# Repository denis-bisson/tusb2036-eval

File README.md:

Evaluation board for the TI TUSB2036 USB hub controller.

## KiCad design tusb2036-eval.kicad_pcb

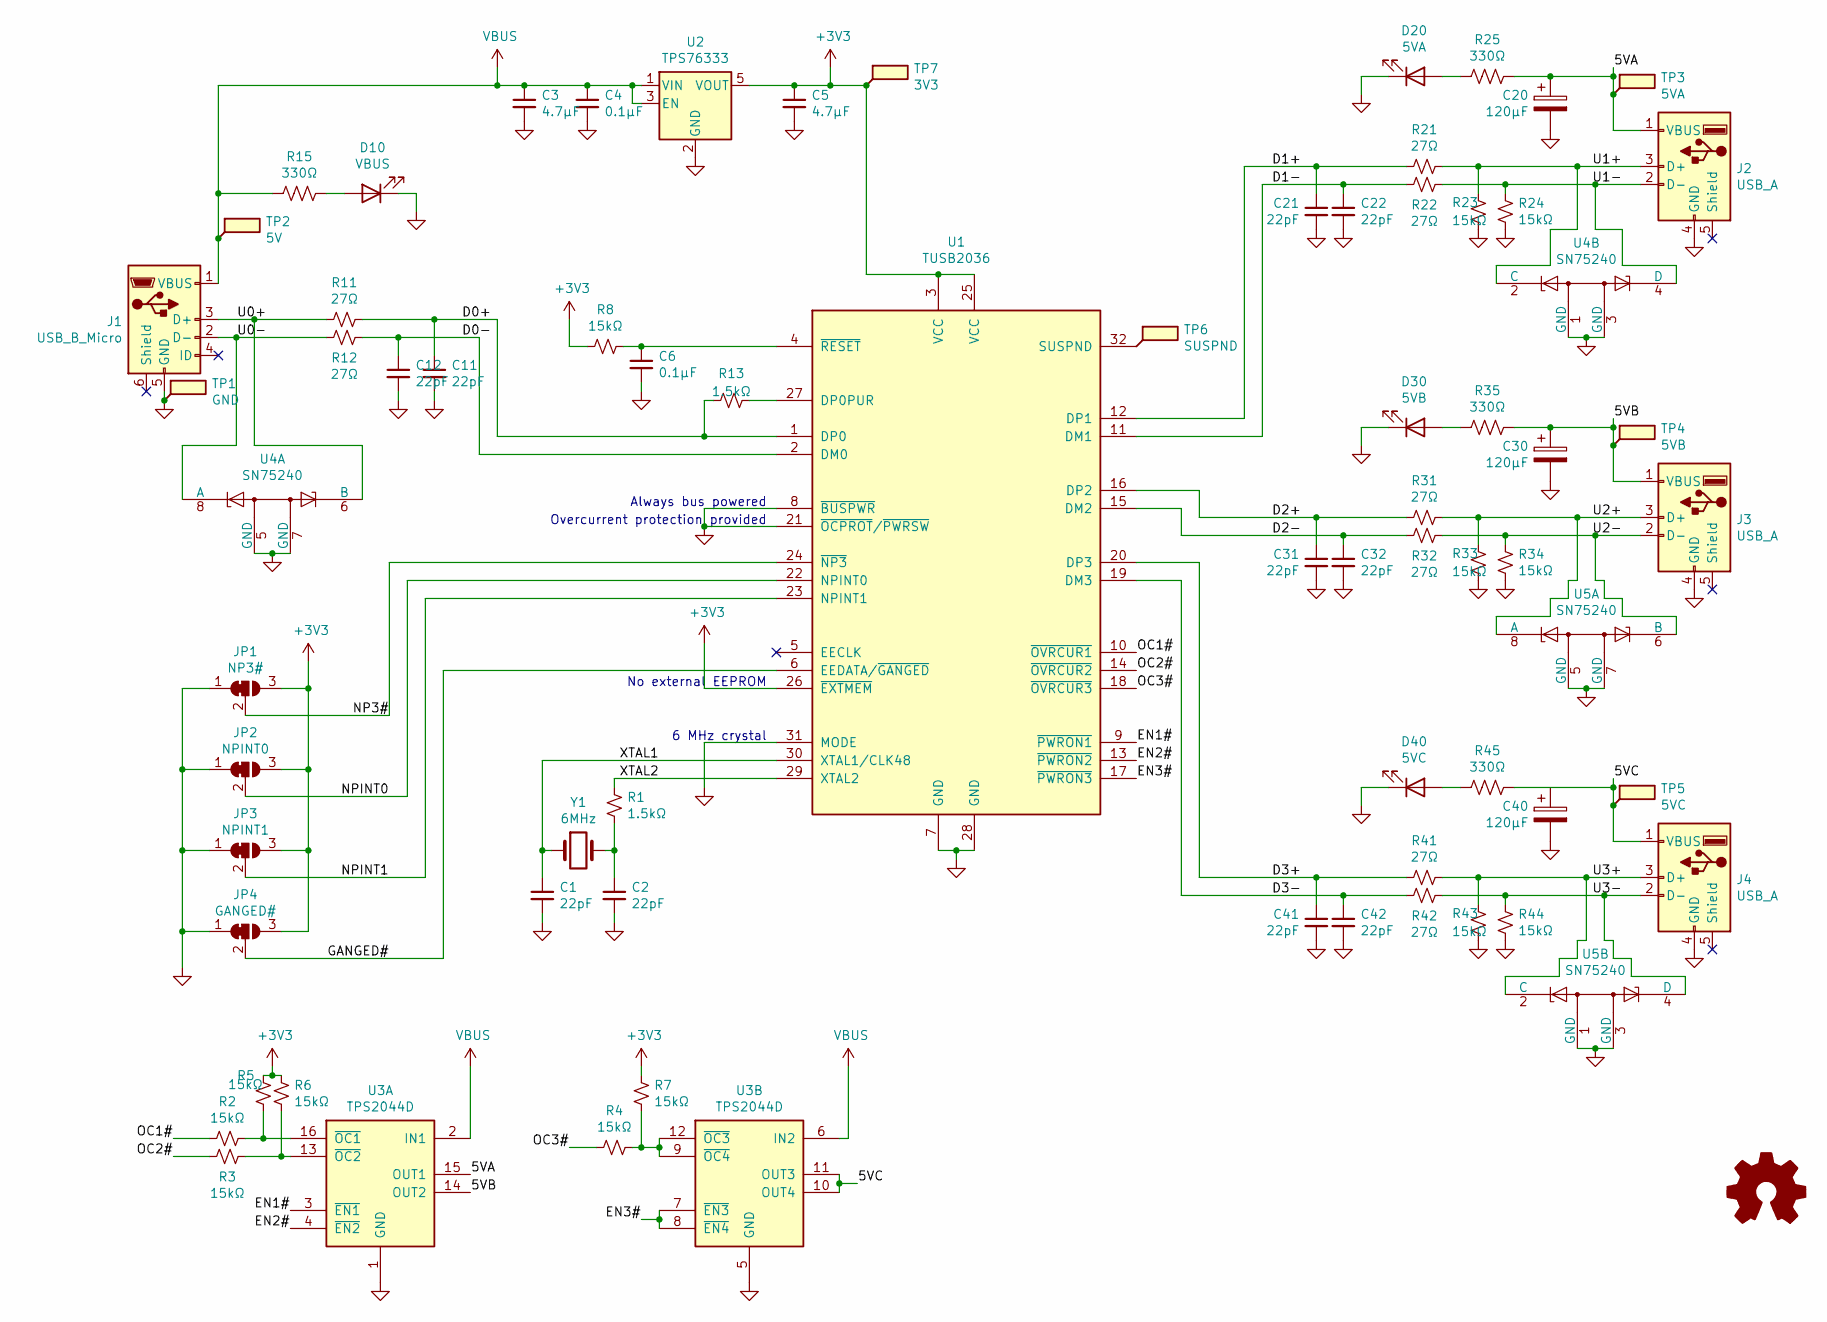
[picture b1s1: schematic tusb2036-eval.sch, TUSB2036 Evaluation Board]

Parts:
C1, C2, C11, C12, C21, C22, C31, C32, C41, C42: 22pF; C_1206_3216Metric
C3, C5: 4.7μF; C_1206_3216Metric
C4, C6: 0.1μF; C_1206_3216Metric
C20, C30, C40: 120μF; CAPPM7343X310N
D10: VBUS; LED_1206_3216Metric
D20: 5VA; LED_1206_3216Metric
D30: 5VB; LED_1206_3216Metric
D40: 5VC; LED_1206_3216Metric
J1: USB_B_Micro; UJ2-MIBH-4-SMT
J2, J3, J4: USB_A; 62900416021
JP1: NP3#; PinHeader_1x03_P2.54mm_Vertical
JP2: NPINT0; PinHeader_1x03_P2.54mm_Vertical
JP3: NPINT1; PinHeader_1x03_P2.54mm_Vertical
JP4: GANGED#; PinHeader_1x03_P2.54mm_Vertical
LOGO1: Logo_Open_Hardware_Small; OSHW-Logo2_9.8x8mm_SilkScreen
R1, R13: 1.5kΩ; R_1206_3216Metric
R2, R3, R4, R5, R6, R7, R8, R23, R24, R33, R34, R43, R44: 15kΩ; R_1206_3216Metric
R11, R12, R21, R22, R31, R32, R41, R42: 27Ω; R_1206_3216Metric
R15, R25, R35, R45: 330Ω; R_1206_3216Metric
TP1: GND; TestPoint_Pad_D2.0mm
TP2: 5V; TestPoint_Pad_D2.0mm
TP3: 5VA; TestPoint_Pad_D2.0mm
TP4: 5VB; TestPoint_Pad_D2.0mm
TP5: 5VC; TestPoint_Pad_D2.0mm
TP6: SUSPND; TestPoint_Pad_D2.0mm
TP7: 3V3; TestPoint_Pad_D2.0mm
U1: TUSB2036; LQFP-32_7x7mm_P0.8mm
U2: TPS76333; SOT-23-5
U3: TPS2044D; SOIC-16_3.9x9.9mm_P1.27mm
U4, U5: SN75240; TSSOP-8_4.4x3mm_P0.65mm
Y1: 6MHz; Crystal_SMD_HC49-SD

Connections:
+3V3: C5.1, JP1.3 (B), JP2.3 (B), JP3.3 (B), JP4.3 (B), R5.2, R6.2, R7.2, R8.2, TP7.1, U1.3 (VCC), U1.25 (VCC), U1.26 (~EXTMEM), U2.5 (VOUT)
/5VA: C20.1, J2.1 (VBUS), R25.1, TP3.1, U3.15 (OUT1)
/5VB: C30.1, J3.1 (VBUS), R35.1, TP4.1, U3.14 (OUT2)
/5VC: C40.1, J4.1 (VBUS), R45.1, TP5.1, U3.10 (OUT4), U3.11 (OUT3)
/D0+: C11.1, R11.2, R13.2, U1.1 (DP0)
/D0-: C12.1, R12.2, U1.2 (DM0)
/D1+: C21.1, R21.1, U1.12 (DP1)
/D1-: C22.1, R22.1, U1.11 (DM1)
/D2+: C31.1, R31.1, U1.16 (DP2)
/D2-: C32.1, R32.1, U1.15 (DM2)
/D3+: C41.1, R41.1, U1.20 (DP3)
/D3-: C42.1, R42.1, U1.19 (DM3)
/EN1#: U1.9 (~PWRON1), U3.3 (~EN1)
/EN2#: U1.13 (~PWRON2), U3.4 (~EN2)
/EN3#: U1.17 (~PWRON3), U3.7 (~EN3), U3.8 (~EN4)
/GANGED#: JP4.2 (C), U1.6 (EEDATA/~GANGED)
/NP3#: JP1.2 (C), U1.24 (~NP3)
/NPINT0: JP2.2 (C), U1.22 (NPINT0)
/NPINT1: JP3.2 (C), U1.23 (NPINT1)
/OC1#: R2.2, U1.10 (~OVRCUR1)
/OC2#: R3.2, U1.14 (~OVRCUR2)
/OC3#: R4.2, U1.18 (~OVRCUR3)
/U0+: J1.3 (D+), R11.1, U4.6 (B)
/U0-: J1.2 (D-), R12.1, U4.8 (A)
/U1+: J2.3 (D+), R21.2, R23.1, U4.2 (C)
/U1-: J2.2 (D-), R22.2, R24.1, U4.4 (D)
/U2+: J3.3 (D+), R31.2, R33.1, U5.8 (A)
/U2-: J3.2 (D-), R32.2, R34.1, U5.6 (B)
/U3+: J4.3 (D+), R41.2, R43.1, U5.2 (C)
/U3-: J4.2 (D-), R42.2, R44.1, U5.4 (D)
/XTAL1: C1.1, U1.30 (XTAL1/CLK48), Y1.1
/XTAL2: R1.1, U1.29 (XTAL2)
GND: C1.2, C2.2, C3.2, C4.2, C5.2, C6.2, C11.2, C12.2, C20.2, C21.2, C22.2, C30.2, C31.2, C32.2, C40.2, C41.2, C42.2, D10.1 (K), D20.1 (K), D30.1 (K), D40.1 (K), J1.5 (GND), J2.4 (GND), J3.4 (GND), J4.4 (GND), JP1.1 (A), JP2.1 (A), JP3.1 (A), JP4.1 (A), R23.2, R24.2, R33.2, R34.2, R43.2, R44.2, TP1.1, U1.7 (GND), U1.8 (~BUSPWR), U1.21 (~OCPROT~/~PWRSW~), U1.28 (GND), U1.31 (MODE), U2.2 (GND), U3.1 (GND), U3.5 (GND), U4.1 (GND), U4.3 (GND), U4.5 (GND), U4.7 (GND), U5.1 (GND), U5.3 (GND), U5.5 (GND), U5.7 (GND)
unnamed: C2.1, R1.2, Y1.2
unnamed: C6.1, R8.1, U1.4 (~RESET)
unnamed: D10.2 (A), R15.1
unnamed: D20.2 (A), R25.2
unnamed: D30.2 (A), R35.2
unnamed: D40.2 (A), R45.2
unnamed: R2.1, R5.1, U3.16 (~OC1)
unnamed: R3.1, R6.1, U3.13 (~OC2)
unnamed: R4.1, R7.1, U3.9 (~OC4), U3.12 (~OC3)
unnamed: R13.1, U1.27 (DP0PUR)
unnamed: TP6.1, U1.32 (SUSPND)
VBUS: C3.1, C4.1, J1.1 (VBUS), R15.2, TP2.1, U2.1 (VIN), U2.3 (EN), U3.2 (IN1), U3.6 (IN2)

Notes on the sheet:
Always bus powered
Overcurrent protection provided
No external EEPROM
6 MHz crystal

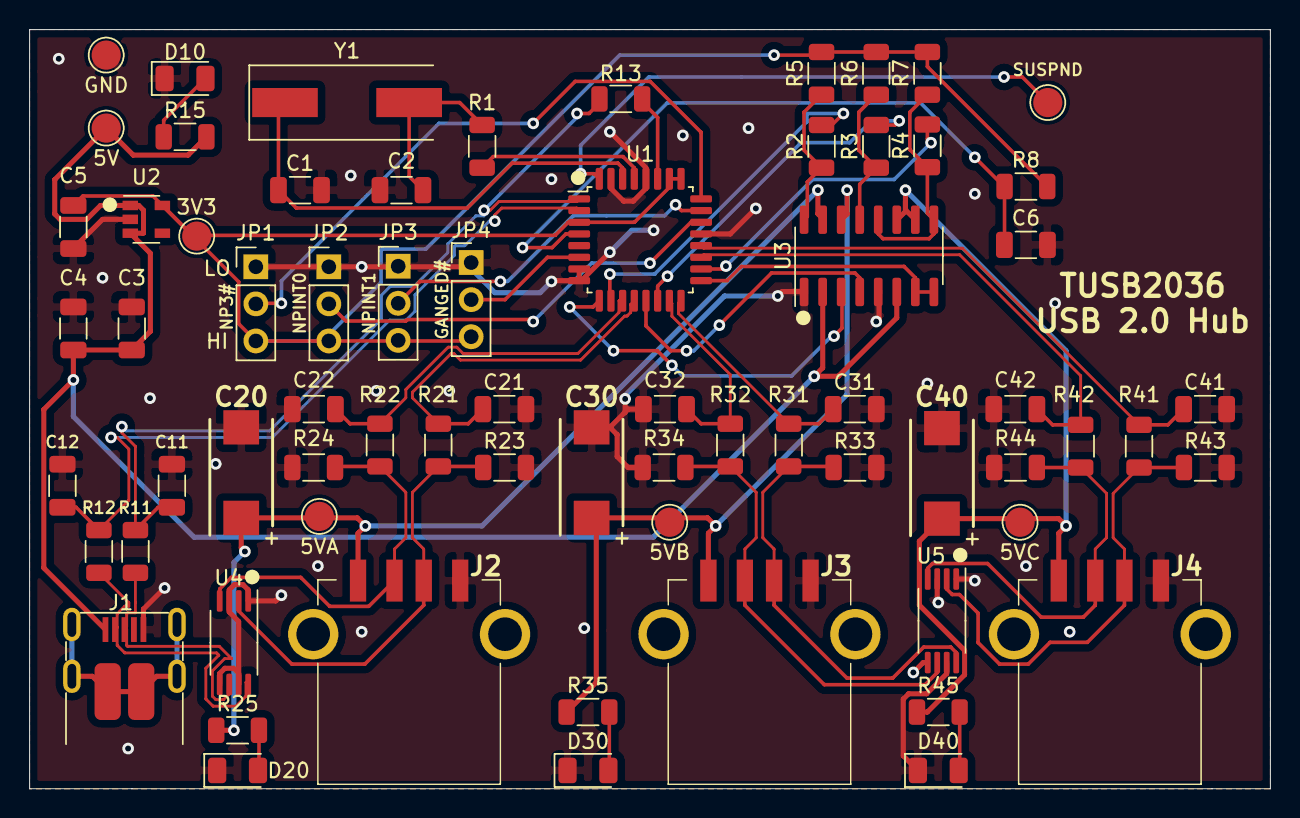
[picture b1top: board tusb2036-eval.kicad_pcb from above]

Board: 2 copper layers, 85.0 x 52.0 mm, 70 parts (1 on the bottom side), 45 nets.

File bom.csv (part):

Refs,value,Vendor,Vendor Part #,Price,datasheet,footprint
C1,22pF,Mouser,710-885012009007,0.61,https://www.mouser.com/datasheet/2/445/885012009007-1727300.pdf,Capacitor_SMD:C_1206_3216Metric
C10,22pF,Mouser,710-885012009007,0.61,https://www.mouser.com/datasheet/2/445/885012009007-1727300.pdf,Capacitor_SMD:C_1206_3216Metric
C11,22pF,Mouser,710-885012009007,0.61,https://www.mouser.com/datasheet/2/445/885012009007-1727300.pdf,Capacitor_SMD:C_1206_3216Metric
C2,22pF,Mouser,710-885012009007,0.61,https://www.mouser.com/datasheet/2/445/885012009007-1727300.pdf,Capacitor_SMD:C_1206_3216Metric
C20,120μF,Mouser,74-293D127X96R3D2TE3,0.87,https://www.mouser.com/datasheet/2/427/293d-1763499.pdf,Vishay:CAPPM7343X310N
C21,22pF,Mouser,710-885012009007,0.61,https://www.mouser.com/datasheet/2/445/885012009007-1727300.pdf,Capacitor_SMD:C_1206_3216Metric
C22,22pF,Mouser,710-885012009007,0.61,https://www.mouser.com/datasheet/2/445/885012009007-1727300.pdf,Capacitor_SMD:C_1206_3216Metric
C3,4.7μF,Mouser,80-C1210C475J3N,0.93,https://www.mouser.com/datasheet/2/212/KEM_C1008_X8L_150C_SM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,Capacitor_SMD:C_1206_3216Metric
C30,120μF,Mouser,74-293D127X96R3D2TE3,0.87,https://www.mouser.com/datasheet/2/427/293d-1763499.pdf,Vishay:CAPPM7343X310N
C31,22pF,Mouser,710-885012009007,0.61,https://www.mouser.com/datasheet/2/445/885012009007-1727300.pdf,Capacitor_SMD:C_1206_3216Metric
C32,22pF,Mouser,710-885012009007,0.61,https://www.mouser.com/datasheet/2/445/885012009007-1727300.pdf,Capacitor_SMD:C_1206_3216Metric
C4,0.1μF,Mouser,581-12105C104JAT2A,0.46,https://www.mouser.com/datasheet/2/40/X7RDielectric-777024.pdf,Capacitor_SMD:C_1206_3216Metric
C40,120μF,Mouser,74-293D127X96R3D2TE3,0.87,https://www.mouser.com/datasheet/2/427/293d-1763499.pdf,Vishay:CAPPM7343X310N
C41,22pF,Mouser,710-885012009007,0.61,https://www.mouser.com/datasheet/2/445/885012009007-1727300.pdf,Capacitor_SMD:C_1206_3216Metric
C42,22pF,Mouser,710-885012009007,0.61,https://www.mouser.com/datasheet/2/445/885012009007-1727300.pdf,Capacitor_SMD:C_1206_3216Metric
C5,4.7μF,Mouser,80-C1210C475J3N,0.93,https://www.mouser.com/datasheet/2/212/KEM_C1008_X8L_150C_SM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,Capacitor_SMD:C_1206_3216Metric
J1,USB_B_Micro,Mouser,490-UJ2-MIBH-4-SMT,0.79,https://www.mouser.com/datasheet/2/670/uj2_mibh_4_smt-1313358.pdf,CUI:UJ2-MIBH-4-SMT
J2,USB_A,Mouser,710-62900416021,2.36,https://www.mouser.com/datasheet/2/445/62900416021-1718169.pdf,Wurth:62900416021
J3,USB_A,Mouser,710-62900416021,2.36,https://www.mouser.com/datasheet/2/445/62900416021-1718169.pdf,Wurth:62900416021
J4,USB_A,Mouser,710-62900416021,2.36,https://www.mouser.com/datasheet/2/445/62900416021-1718169.pdf,Wurth:62900416021
JP1,NP3_SEL,Mouser,649-1012937890301BLF,0.1,https://www.amphenol-icc.com/media/wysiwyg/files/documentati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,Connector_PinHeader_2.54mm:PinHeader_1x03_P2.54mm_Vertical
JP2,NPINT0_SEL,Mouser,649-1012937890301BLF,0.1,https://www.amphenol-icc.com/media/wysiwyg/files/documentati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,Connector_PinHeader_2.54mm:PinHeader_1x03_P2.54mm_Vertical
JP3,NPINT1_SEL,Mouser,649-1012937890301BLF,0.1,https://www.amphenol-icc.com/media/wysiwyg/files/documentati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,Connector_PinHeader_2.54mm:PinHeader_1x03_P2.54mm_Vertical
JP4,GANGED_SEL,Mouser,649-1012937890301BLF,0.1,https://www.amphenol-icc.com/media/wysiwyg/files/documentati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,Connector_PinHeader_2.54mm:PinHeader_1x03_P2.54mm_Vertical
R1,1.5kΩ,Mouser,603-RC1210FR-071K5L,0.14,https://www.mouser.com/datasheet/2/447/PYu_RC_Group_51_RoHS_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,Resistor_SMD:R_1206_3216Metric
R10,27Ω,Mouser,603-RC1210FR-0727RL,0.14,https://www.mouser.com/datasheet/2/447/PYu_RC_Group_51_RoHS_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,Resistor_SMD:R_1206_3216Metric
R11,27Ω,Mouser,603-RC1210FR-0727RL,0.14,https://www.mouser.com/datasheet/2/447/PYu_RC_Group_51_RoHS_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,Resistor_SMD:R_1206_3216Metric
R2,1.5kΩ,Mouser,603-RC1210FR-071K5L,0.14,https://www.mouser.com/datasheet/2/447/PYu_RC_Group_51_RoHS_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,Resistor_SMD:R_1206_3216Metric
R21,27Ω,Mouser,603-RC1210FR-0727RL,0.14,https://www.mouser.com/datasheet/2/447/PYu_RC_Group_51_RoHS_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,Resistor_SMD:R_1206_3216Metric
R22,27Ω,Mouser,603-RC1210FR-0727RL,0.14,https://www.mouser.com/datasheet/2/447/PYu_RC_Group_51_RoHS_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,Resistor_SMD:R_1206_3216Metric
R23,15kΩ,Mouser,603-RC1210FR-0715KL,0.16,https://www.mouser.com/datasheet/2/447/PYu_RC_Group_51_RoHS_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,Resistor_SMD:R_1206_3216Metric
R24,15kΩ,Mouser,603-RC1210FR-0715KL,0.16,https://www.mouser.com/datasheet/2/447/PYu_RC_Group_51_RoHS_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,Resistor_SMD:R_1206_3216Metric
R3,15kΩ,Mouser,603-RC1210FR-0715KL,0.16,https://www.mouser.com/datasheet/2/447/PYu_RC_Group_51_RoHS_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,Resistor_SMD:R_1206_3216Metric
R31,27Ω,Mouser,603-RC1210FR-0727RL,0.14,https://www.mouser.com/datasheet/2/447/PYu_RC_Group_51_RoHS_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,Resistor_SMD:R_1206_3216Metric
R32,27Ω,Mouser,603-RC1210FR-0727RL,0.14,https://www.mouser.com/datasheet/2/447/PYu_RC_Group_51_RoHS_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,Resistor_SMD:R_1206_3216Metric
R33,15kΩ,Mouser,603-RC1210FR-0715KL,0.16,https://www.mouser.com/datasheet/2/447/PYu_RC_Group_51_RoHS_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,Resistor_SMD:R_1206_3216Metric
R34,15kΩ,Mouser,603-RC1210FR-0715KL,0.16,https://www.mouser.com/datasheet/2/447/PYu_RC_Group_51_RoHS_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,Resistor_SMD:R_1206_3216Metric
R41,27Ω,Mouser,603-RC1210FR-0727RL,0.14,https://www.mouser.com/datasheet/2/447/PYu_RC_Group_51_RoHS_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,Resistor_SMD:R_1206_3216Metric
R42,27Ω,Mouser,603-RC1210FR-0727RL,0.14,https://www.mouser.com/datasheet/2/447/PYu_RC_Group_51_RoHS_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,Resistor_SMD:R_1206_3216Metric
R43,15kΩ,Mouser,603-RC1210FR-0715KL,0.16,https://www.mouser.com/datasheet/2/447/PYu_RC_Group_51_RoHS_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,Resistor_SMD:R_1206_3216Metric
R44,15kΩ,Mouser,603-RC1210FR-0715KL,0.16,https://www.mouser.com/datasheet/2/447/PYu_RC_Group_51_RoHS_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,Resistor_SMD:R_1206_3216Metric
SW1,RESET,Mouser,653-B3FS-1002P,0.58,https://www.mouser.com/datasheet/2/307/omron_B3FS-1189765.pdf,Omron:SW_SPST_Omron_B3FS-100xP
U1,TUSB2036,Mouser,595-TUSB2036VFR,3.4,http://www.ti.com/lit/ds/symlink/tusb2036.pdf,Package_QFP:LQFP-32_7x7mm_P0.8mm
U2,TPS76333,Mouser,595-PS76333QDBVRG4Q1,1,http://www.ti.com/lit/ds/symlink/tps763.pdf,Package_TO_SOT_SMD:SOT-23-5
U3,TPS2044D,Mouser,595-TPS2044BDR,2.73,http://www.ti.com/lit/ds/symlink/tps2044.pdf,Package_SO:SOIC-16_3.9x9.9mm_P1.27mm
U4,SN75240,Mouser,595-SN75240PWR,1.31,http://www.ti.com/lit/ds/symlink/sn65220.pdf,Package_SO:TSSOP-8_4.4x3mm_P0.65mm
U5,SN75240,Mouser,595-SN75240PWR,1.31,http://www.ti.com/lit/ds/symlink/sn65220.pdf,Package_SO:TSSOP-8_4.4x3mm_P0.65mm
Y1,6MHz,Mouser,73-XT49M600-20,0.95,https://www.mouser.com/datasheet/2/427/xt49m-1763016.pdf,Crystal:Crystal_SMD_HC49-SD
C12,22pF,Mouser,710-885012009007,0.61,https://www.mouser.com/datasheet/2/445/885012009007-1727300.pdf,Capacitor_SMD:C_1206_3216Metric
D10,VBUS,Mouser,604-AP3216ID,0.28,https://www.mouser.com/datasheet/2/216/ap3216id-1173252.pdf,LED_SMD:LED_1206_3216Metric
D20,5VA,Mouser,604-AP3216ID,0.28,https://www.mouser.com/datasheet/2/216/ap3216id-1173252.pdf,LED_SMD:LED_1206_3216Metric
D30,5VB,Mouser,604-AP3216ID,0.28,https://www.mouser.com/datasheet/2/216/ap3216id-1173252.pdf,LED_SMD:LED_1206_3216Metric
D40,5VC,Mouser,604-AP3216ID,0.28,https://www.mouser.com/datasheet/2/216/ap3216id-1173252.pdf,LED_SMD:LED_1206_3216Metric
LOGO1,Logo_Open_Hardware_Small,-,-,0,-,Symbol:OSHW-Logo2_9.8x8mm_SilkScreen
R12,27Ω,Mouser,603-RC1210FR-0727RL,0.14,https://www.mouser.com/datasheet/2/447/PYu_RC_Group_51_RoHS_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,Resistor_SMD:R_1206_3216Metric
R15,330Ω,Mouser,667-ERJ-8ENF3300V,0.10,https://www.mouser.com/datasheet/2/315/AOA0000C304-1149620.pdf,Resistor_SMD:R_1206_3216Metric
R25,330Ω,Mouser,667-ERJ-8ENF3300V,0.10,https://www.mouser.com/datasheet/2/315/AOA0000C304-1149620.pdf,Resistor_SMD:R_1206_3216Metric
R35,330Ω,Mouser,667-ERJ-8ENF3300V,0.10,https://www.mouser.com/datasheet/2/315/AOA0000C304-1149620.pdf,Resistor_SMD:R_1206_3216Metric
R45,330Ω,Mouser,667-ERJ-8ENF3300V,0.10,https://www.mouser.com/datasheet/2/315/AOA0000C304-1149620.pdf,Resistor_SMD:R_1206_3216Metric
TP1,GND,-,-,0,-,TestPoint:TestPoint_Pad_D2.0mm
TP2,5V,-,-,0,-,TestPoint:TestPoint_Pad_D2.0mm
TP3,5VA,-,-,0,-,TestPoint:TestPoint_Pad_D2.0mm
TP4,5VB,-,-,0,-,TestPoint:TestPoint_Pad_D2.0mm
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
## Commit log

2021-03-21 TUSB2036 Eval board v1
2021-03-21 Add schematic and render
2021-03-21 Fix 120uF caps
2021-03-21 Add shunts to BOM
2021-03-22 Rename demo to eval
2021-03-22 Add datasheet
2021-03-23 Add R3 to disable TPS2044 OUT4
2021-03-23 Update BOM
2021-04-04 Convert BOM from one per line to grouped
2021-04-05 Thicker power traces and fix 3D models
2021-04-05 Add label for test point
2021-04-15 Add CC-BY-4.0 license
2021-04-15 Fix up libraries
2021-04-15 Replace micro USB connector
    The Molex is difficult to hand solder, so swapping that out for the CUI
2021-04-15 Add CUI USB 3D model
2021-04-16 Add test points
2021-04-19 Fix button footprint and other small updates
2021-04-19 Adjust silkscreen
2021-04-19 Fix BOM
2021-04-24 Add OSHW logo
2021-04-27 Add LEDs
2021-04-28 Clean up schematic
    * Start using # for active-low nets
    * Rearrange config block for readability
    * Remove some pull-up resistors that I'm not sure about
2021-04-28 Add some components from TUSB2036-EVL user guide
2021-04-28 Implement overcurrent resistor changes
2021-05-04 Add RC filter for RESET
    Suggested by eevblog user pigrew and example schematic

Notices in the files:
tusb2036-eval.kicad_pcb:
Licensed under Creative Commons CC-BY-4.0
